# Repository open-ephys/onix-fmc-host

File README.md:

# ONIX FMC Host
This card provides a host interface for serialized headstages and miniscopes, as
well as general purpose analog and digital IO. It is a VITA-57.1
compliant module that uses high pin-count FMC connector. In combination with a
base FPGA board (e.g. [Numato Lab
Nereid](https://numato.com/product/nereid-kintex-7-pci-express-fpga-development-board),
it provides host PC communication for the following:

- Two deserailizers for any multifunction headstage conforming to the ONIX
  serialization protocol
- 12x 16-bit, +/-10V analog outputs or inputs. Direction selected via analog
  switch controllable over the FMC connector. Analog inputs are separated into
  2 simultaneously sampled 6-channel banks. 
- Analog output are always looped back using the analog inputs.
- 3x high speed LVDS input pairs
- 2x high speed LVDS outputs pairs
- 2x high speed, arbitrary logic-level, singled-ended Hi-Z or 50-ohm clock inputs
- 1x high speed single ended, 50-ohm clock output
- 4x MLVDS input or output trigger lines

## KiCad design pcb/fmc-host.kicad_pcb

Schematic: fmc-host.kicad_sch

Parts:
C1, C2, C5, C6, C26, C27, C34, C35, C36, C37, C70, C71, C72, C73, C79, C80, C81, C91, C92, C106, C118, C139, C140: 10uF; 1206; MPN GRM31CR71E106KA12L
C3, C4, C7, C8, C9, C10, C13, C14, C15, C16, C17, C18, C19, C22, C23, C30, C31, C32, C33, C41, C43, C44, C45, C46, C47, C48, C49, C52, C53, C54, C55, C56, C60, C61, C63, C65, C67, C68, C78, C83, C84, C85, C86, C87, C89, C90, C93, C99, C100, C104, C107, C110, C111, C112, C114, C132, C134, C135, C137, C138, C141, C142: 0.1uF; 0402; Voltage 25V; MPN GRM155R71E104KE14D
C11, C12, C20, C21, C24, C25, C50, C51, C57, C58, C82, C122, C123, C124: 10nF; 0402; MPN GCM155R71E103KA37D
C28, C29: 4.7nF; 0402; MPN CC0402KRX7R8BB472
C38, C39: 47nF; 0402; MPN GRM155R71E473KA88D
C40, C42, C64, C66, C74, C75, C76, C88: 1uF; 0805; MPN GCM21BR71E105KA56L
C59, C62, C69, C77, C95, C96, C101, C103, C105, C108, C109, C113, C116, C117, C119, C120, C121, C125, C126, C127: 10uF; 0805; MPN GRM21BR61E106KA73L
C94, C97, C98, C102, C130, C131: 47uF; 1210; MPN TMK325ABJ476MM-T
C115: 100pF; 0402; MPN CC0402JRNPO9BN101
C128, C129: 0.1uF, 500V; 1210; MPN C1210C104KCRACTU
C133, C136: 33uF; 1411-VISHAY-B; MPN TL8B0336M020C
D1, D2: SESD0402X1UN-0030-088; 0402P-DFN; MPN SESD0402X1UN-0030-088
D3, D4, D5: BAR66; SOT23; MPN BAR66E6327HTSA1
D6: KDZVTR4.3B; SOD123; MPN KDZVTR4.3B
F1, F2, F3: C014F-2; 1812; MPN MINISMDC014F-2
J1, J2, J3, J4, J5: 6-1634010-0; MMCX-THRU; MPN 262105
J6: FTSH-105-01-F-D-RA-K; MPN FTSH-105-01-F-D-RA-K
J7: 12226-8250-00FR; 12226-82X0-00XX; MPN 12226-8250-00FR
J8: FMC_SINGLE_WIDTH_MODULE; not fitted
J9: ASP-134488-01; FMC_HPC_MALE; MPN ASP-134488-01
J10: BM08B-SURS-TF; MPN BM08B-SURS-TF
L1, L2: 1008PS-472; 1008PS; MPN 1008PS-472KLC
L3, L4, L9, L10, L11, L12: BLM18KG601SN1D; 0603; MPN BLM18KG601SN1D
L5, L6: SRN6045TA-101M; SRN6045TA; MPN SRN6045TA-101M
L7, L8: MPZ2012S102AT000; 0805; MPN MPZ2012S102AT000
L13: 1277AS-H-6R8M=P2; 1210; MPN 1277AS-H-6R8M=P2
L14, L15, L16, L17, L18, L19: BLM15PX601SN1D; 0402; MPN BLM15PX601SN1D
Q1, Q2, Q3, Q4: SI1012R; SC75; MPN SI1012CR-T1-GE3
R1, R2, R38, R39: 3k; 0402; MPN ERJ-2RKF3001X
R3, R4, R9, R10, R57, R58: 2k; 0402; MPN ERJ-2RKF2001X
R5, R6, R7, R8, R11, R12: 150,0.25W; 0603; MPN CRGP0603F150R
R13, R14, R49, R50, R51, R52, R76, R83, R84: 165k; 0402; MPN ERJ-2RKF1653X
R15, R16, R35, R37, R59, R63, R64, R65, R67, R68, R78, R79, R82: 10k; 0402; MPN ERJ-2RKF1002X
R17, R18, R41, R42, R44, R45, R46, R47: 1k; 0402; MPN ERJ-2RKF1001X
R19, R21: 5.6k 1%; 0402; MPN ERJ-2RKF5601X
R20, R22: 21k 1%; 0402; MPN ERJ-2RKF2102X
R23, R24, R28, R29: 49.9; 0402; MPN RR0510R-49R9-D
R25, R26, R27: 100; 0402; MPN ERJ-2RKF1000X
R30, R31, R32, R33, R40, R43, R71, R73, R75: 4.7k; 0402; MPN ERJ-2RKF4701X
R34, R36: DNP; 0402; MPN DNP; not fitted
R48, R66: 0; 0402; MPN RC0402JR-070RL
R53, R54, R55, R56: 2.2k; RN2X8-1506; MPN EXB-2HV222JV
R60, R61: 3.48k; 0402; MPN ERJ-2RKF3481X
R62: 649k; 0402; MPN ERJ-2RKF6493X
R69: 2.2k; 0402; MPN ERJ-2RKF2201X
R70: 15k; 0402; MPN ERJ-2RKF1502X
R72, R74: 47k; 0402; MPN ERJ-2RKF4702X
R77: 178k; 0402; MPN ERJ-2RKF1783X
R80, R81: 73.2k; 0402; MPN ERJ-2RKF7322X
R289, R290: 4.7,1W; R_1206_3216Metric; MPN SG73P2BTTD4R7J
S1, S2: CHS-01TA; DIP01-SMD-GULL; MPN CHS-01TA; not fitted
S3: CHS-02TB; MPN CHS-02TB
TP1, TP2, TP4, TP5, TP6, TP7, TP11, TP12, TP13, TP14, TP15, TP16: TPB1,27; B1,27
TP3, TP8, TP9, TP10, TP17, TP18: TPB2,54; B2,54
U1: SN74LVC2G34DCKR; SC70; MPN SN74LVC2G34DCKR
U2: SN65LVDS9638DGN; MSOP-8-PAD-3X3; MPN SN65LVDS9638DGN
U3: FIN1032MTCX; TSSOP-16; MPN FIN1032MTCX
U4, U5: ADCMP600; SOT-23-5; MPN ADCMP600BRJZ-R2
U6, U7, U8: DG1412E; QFN16-4X4MM; MPN DG1412EEN-T1-GE4
U9, U10: DS90UB934-Q1; WQFN48-7X7-PAD; MPN DS90UB934TRGZRQ1
U11: DS91M040; WQFN32-5X5; MPN DS91M040TSQ/NOPB
U12: AD5766BCPZ-RL7; CP_40_7; MPN AD5766BCPZ-RL7
U13: MCP47FEB02A0-E/ST; TSSOP-8; MPN MCP47FEB02A0-E/ST
U14: LM4132AMF-2.5/NOPB; SOT-23-5; MPN LM4132AMF-2.5/NOPB
U15: AD7616BSTZ; ST_80_2; MPN AD7616BSTZ
U16: AD5142BRUZ10; TSSOP-16_4.4X5.0; MPN AD5142BRUZ10
U17: LTM4622A; BGA_5X5_625X625; MPN LTM4622AIY#PBF
U18, U25, U26: D3V3XA4B10LP; Diodes_UDFN-10_1.0x2.5mm_P0.5mm; MPN D3V3XA4B10LP-7
U19, U20: TPS7A49; PVSON-N8+4-3X3; MPN TPS7A4901DRBR
U21: TPS7A30; PVSON-N8+4-3X3; MPN TPS7A3001DRBT
U22: 24AA64-I/ST; TSSOP8; MPN 24AA64-I/ST
U23: LTM8049IY#PBF; LTM8049; MPN LTM8049IY#PBF
U24: TPS62061DSGT; WSON8-2X2; MPN TPS62061DSGT
U27: TLV9062IDSGR; WSON-8-1EP_2x2mm_P0.5mm_EP0.9x1.6mm; MPN TLV9062IDSGR
U28: SN74LVC2G14DBV; SOT-23-6; MPN SN74LVC2G14DBVR
X2: OE-LOGO_7X5; OE-LOGO-7X5

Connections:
+1V8: C86.2, C87.2, C91.2, C92.2, C106.2, L3.2, L4.2, L9.1, L10.1, L13.1, R19.1, R21.1, R34.1, R36.1, TP16.TP (TP_TP), U9.17 (VDD18), U10.17 (VDD18), U24.4 (FB)
+3V3: C10.2, C22.1, C23.1, C28.1, C29.1, C32.1, C33.1, C74.2, C78.2, C82.2, C89.2, C93.2, C96.2, C111.2, C113.2, C114.2, C117.2, C118.2, C136.A (+), C137.2, C138.2, C139.1, C140.1, C141.1, C142.1, J9.E39 (VADJ@1), J9.F40 (VADJ@2), J9.G39 (VADJ@1), J9.H40 (VADJ@2), J9.J39 (VIO_B_M2C@1), J9.K40 (VIO_B_M2C@2), L11.1, L12.1, R30.2, R31.2, R32.2, R33.2, R40.2, R43.2, R57.2, R58.2, R64.1, R65.1, R69.1, R78.2, R79.2, S1.2, S2.2, TP11.TP (TP_TP), U1.5 (VCC), U2.1 (VCC), U3.4 (EN), U3.16 (VCC), U4.5 (V+), U5.5 (V+), U9.4 (OSS_SEL), U9.5 (OEN), U10.4 (OSS_SEL), U10.5 (OEN), U11.11 (VDD), U11.12 (VDD), U11.29 (VDD), U11.30 (VDD), U12.4 (VLOGIC), U13.1 (VDD), U13.2 (REFA), U15.49 (VDRIVE), U16.1 (INDEP), U16.11 (VDD), U16.12 (VLOGIC), U23.A5 (VIN1), U23.A6 (VIN1), U23.A7 (VIN1), U23.B7 (RUN1), U23.K7 (RUN2), U23.L5 (VIN2), U23.L6 (VIN2), U23.L7 (VIN2), U24.5 (EN), U24.6 (MODE), U24.7 (AVIN), U24.8 (PVIN), U27.8 (V+), U28.5 (V_{CC})
+12V: C116.2, C133.A (+), C134.2, C135.2, J7.1, J7.26, J9.C35 (12P0V1), J9.C37 (12P0V2), R38.2, R39.2, TP12.TP (TP_TP), U17.A2 (VIN), U17.B3 (VIN), U17.D3 (VIN), U17.E2 (VIN)
/+5V_AN: C59.2, C62.2, C69.2, C77.2, C81.1, C83.2, C84.2, C85.2, C90.2, C107.2, C108.2, L14.1, TP1.TP (TP_TP), U12.28 (AVCC), U14.3 (EN), U14.4 (VIN), U15.6 (VCC), U15.15 (VCC), U15.30 (VCC), U15.71 (VCC)
/+13V_AN: C7.2, C8.2, C9.2, C104.2, C105.2, L15.1, TP2.TP (TP_TP), U6.11 (V+), U7.11 (V+), U8.11 (V+), U12.26 (AVDD)
/-13V_AN: C17.2, C18.2, C19.2, C99.2, C103.2, L16.1, TP4.TP (TP_TP), U6.2 (V-), U6.PAD (V-), U7.2 (V-), U7.PAD (V-), U8.2 (V-), U8.PAD (V-), U12.6 (AVSS), U12.PAD (AVSS)
/ADC_BUSY: J9.J12 (HA11_P), U15.67 (BUSY)
/ADC_CONVST: J9.K13 (HA10_P), U15.68 (CONVST)
/ADC_MISO_A: J9.K11 (HA06_N), U15.57 (DB12/SDOA)
/ADC_MISO_B: J9.J10 (HA07_N), U15.56 (DB11/SDOB)
/ADC_MOSI: J9.K10 (HA06_P), U15.55 (DB10/SDI)
/ADC_SCLK: J9.J13 (HA11_N), U15.62 (SCLK/~RD)
/ADDR0: J9.C27 (LA27_N), R78.1, S3.4
/ADDR1: J9.C26 (LA27_P), R79.1, S3.3
/AIN_AOUT0: J9.F11 (HA08_N), U8.15 (IN1)
/AIN_AOUT1: J9.D11 (LA05_P), U8.6 (IN4)
/AIN_AOUT2: J9.E12 (HA13_P), U8.7 (IN3)
/AIN_AOUT3: J9.H10 (LA04_P), U8.14 (IN2)
/AIN_AOUT4: J9.E18 (HA20_P), U7.15 (IN1)
/AIN_AOUT5: J9.J9 (HA07_P), U7.6 (IN4)
/AIN_AOUT6: J9.G10 (LA03_N), U7.7 (IN3)
/AIN_AOUT7: J9.F17 (HA15_N), U7.14 (IN2)
/AIN_AOUT8: J9.H20 (LA15_N), U6.7 (IN3)
/AIN_AOUT9: J9.J19 (HA18_N), U6.14 (IN2)
/AIN_AOUT10: J9.G19 (LA16_N), U6.6 (IN4)
/AIN_AOUT11: J9.H19 (LA15_P), U6.15 (IN1)
/AIO_0: J7.7, R53.C1, U8.16 (D1)
/AIO_1: J7.20, R53.C3, U8.5 (D4)
/AIO_2: J7.8, R53.C5, U8.8 (D3)
/AIO_3: J7.21, R53.C8, U8.13 (D2)
/AIO_4: J7.9, R54.C4, U7.16 (D1)
/AIO_5: J7.22, R54.C2, U7.5 (D4)
/AIO_6: J7.10, R56.C5, U7.8 (D3)
/AIO_7: J7.23, R56.C7, U7.13 (D2)
/AIO_8: J7.11, R55.C6, U6.8 (D3)
/AIO_9: J7.24, R55.C8, U6.13 (D2)
/AIO_10: J7.12, R55.C4, U6.5 (D4)
/AIO_11: J7.25, R55.C1, U6.16 (D1)
/AOUT0: U6.1 (S1), U12.32 (VOUT0)
/AOUT1: U6.4 (S4), U12.33 (VOUT1)
/AOUT2: U6.9 (S3), U12.34 (VOUT2)
/AOUT3: U6.12 (S2), U12.35 (VOUT3)
/AOUT4: U7.1 (S1), U12.36 (VOUT4)
/AOUT5: U7.4 (S4), U12.37 (VOUT5)
/AOUT6: U7.12 (S2), U12.38 (VOUT6)
/AOUT7: U7.9 (S3), U12.39 (VOUT7)
/AOUT8: U8.9 (S3), U12.12 (VOUT8)
/AOUT9: U8.12 (S2), U12.13 (VOUT9)
/AOUT10: U8.4 (S4), U12.14 (VOUT10)
/AOUT11: U8.1 (S1), U12.15 (VOUT11)
/CLKIN0: J9.D21 (LA17_N_CC), TP7.TP (TP_TP), U4.1 (OUT)
/CLKIN1: J9.E19 (HA20_N), TP6.TP (TP_TP), U5.1 (OUT)
/CLKIN_TERM0: J9.K19 (HA21_P), R17.1
/CLKIN_TERM1: J9.K17 (HA17_N_CC), R18.1
/CLKIN_VBIAS_SCL: J9.J21 (HA22_P), R58.1, U13.7 (SCL)
/CLKIN_VBIAS_SDA: J9.K20 (HA21_N), R57.1, U13.8 (SDA)
/CLKOUT: J9.D20 (LA17_P_CC), U1.1 (IN3), U1.3 (IN2)
/DAC_MISO: J9.K16 (HA17_P_CC), U12.9 (MISO)
/DAC_MOSI: J9.H14 (LA07_N), U12.5 (MOSI)
/DAC_SCLK: J9.J15 (HA14_P), U12.7 (SCLK)
/DES_A_D0: J9.F34 (HB16_P), U10.24 (ROUT0)
/DES_A_D1: J9.K35 (HB14_N), U10.23 (ROUT1)
/DES_A_D2: J9.J34 (HB15_N), U10.22 (ROUT2)
/DES_A_D3: J9.K34 (HB14_P), U10.21 (ROUT3)
/DES_A_D4: J9.E33 (HB19_P), U10.19 (ROUT4)
/DES_A_D5: J9.J33 (HB15_P), U10.18 (ROUT5)
/DES_A_D6: J9.F32 (HB12_N), U10.16 (ROUT6)
/DES_A_D7: J9.E31 (HB13_N), U10.15 (ROUT7)
/DES_A_D8: J9.K32 (HB10_N), U10.14 (ROUT8)
/DES_A_D9: J9.F31 (HB12_P), U10.13 (ROUT9)
/DES_A_D10: J9.J31 (HB11_N), U10.12 (ROUT10)
/DES_A_D11: J9.K31 (HB10_P), U10.11 (ROUT11)
/DES_A_GPIO0: J9.J37 (HB18_N), U10.28 (GPIO0)
/DES_A_GPIO1: J9.K37 (HB17_P_CC), U10.27 (GPIO1)
/DES_A_GPIO2: J9.J36 (HB18_P), U10.26 (GPIO2)
/DES_A_GPIO3: J9.E34 (HB19_N), R43.1, U10.25 (GPIO3/INTB)
/DES_A_HSYNC: J9.E30 (HB13_P), U10.10 (HSYNC)
/DES_A_LOCK: J9.E27 (HB09_P), R50.2, U10.48 (LOCK)
/DES_A_PASS: J9.J28 (HB07_N), R52.2, U10.47 (PASS)
/DES_A_PCLK: J9.K28 (HB06_P_CC), U10.8 (PCLK)
/DES_A_PDB: J9.F35 (HB16_N), U10.30 (PDB)
/DES_A_SCL: J9.F29 (HB08_N), R31.1, U10.2 (SCL)
/DES_A_SDA\: J9.E28 (HB09_N), R33.1, U10.1 (SDA)
/DES_A_VSYNC: J9.J30 (HB11_P), U10.9 (VSYNC)
/DES_B_D0: J9.H29 (LA24_N), U9.24 (ROUT0)
/DES_B_D1: J9.H28 (LA24_P), U9.23 (ROUT1)
/DES_B_D2: J9.G28 (LA25_N), U9.22 (ROUT2)
/DES_B_D3: J9.G27 (LA25_P), U9.21 (ROUT3)
/DES_B_D4: J9.D27 (LA26_N), U9.19 (ROUT4)
/DES_B_D5: J9.D26 (LA26_P), U9.18 (ROUT5)
/DES_B_D6: J9.H26 (LA21_N), U9.16 (ROUT6)
/DES_B_D7: J9.G25 (LA22_N), U9.15 (ROUT7)
/DES_B_D8: J9.H25 (LA21_P), U9.14 (ROUT8)
/DES_B_D9: J9.D24 (LA23_N), U9.13 (ROUT9)
/DES_B_D10: J9.G24 (LA22_P), U9.12 (ROUT10)
/DES_B_D11: J9.D23 (LA23_P), U9.11 (ROUT11)
/DES_B_GPIO0: J9.H32 (LA28_N), U9.28 (GPIO0)
/DES_B_GPIO1: J9.G31 (LA29_N), U9.27 (GPIO1)
/DES_B_GPIO2: J9.H31 (LA28_P), U9.26 (GPIO2)
/DES_B_GPIO3: J9.G30 (LA29_P), R40.1, U9.25 (GPIO3/INTB)
/DES_B_HSYNC\: J9.H23 (LA19_N), U9.10 (HSYNC)
/DES_B_LOCK: J9.J22 (HA22_N), R49.2, U9.48 (LOCK)
/DES_B_PASS: J9.K22 (HA23_P), R51.2, U9.47 (PASS)
/DES_B_PCLK: J9.C22 (LA18_P_CC), U9.8 (PCLK)
/DES_B_PDB: J9.G33 (LA31_P), U9.30 (PDB)
/DES_B_SCL: J9.G22 (LA20_N), R30.1, U9.2 (SCL)
/DES_B_SDA: J9.H22 (LA19_P), R32.1, U9.1 (SDA)
/DES_B_VSYNC: J9.K23 (HA23_N), U9.9 (VSYNC)
/DI_VBIAS0: R15.1, U13.3 (VOUT0)
/DI_VBIAS1: R16.1, U13.4 (VOUT1)
/DOUTP_F_A: C45.2, D2.C, J2.SIG (1), L2.2, R4.2
/DOUTP_F_B: C44.2, D1.C, J1.SIG (1), L1.2, R3.2
/FMC_PG: J9.D1 (PG_C2M), J9.F1 (PG_M2C)
/LINK_A_PWR_EN: J9.H37 (LA32_P), R68.1, U17.B2 (RUN2), U28.1 (1A)
/LINK_B_PWR_EN: J9.K38 (HB17_N_CC), R67.1, U17.D2 (RUN1), U28.3 (2A)
/LINK_PWR_ADJ_MISO: J9.F37 (HB20_P), R69.2, U16.15 (MISO)
/LINK_PWR_ADJ_MOSI: J9.E36 (HB21_P), U16.14 (MOSI)
/LINK_PWR_ADJ_SCLK: J9.H38 (LA32_N), U16.13 (SCLK)
/LVDS_DIN0: J9.J2 (CLK3_M2C_P), U3.3 (AOUT)
/LVDS_DIN0_N: J7.4, R25.1, U3.1 (A-), U18.1, U18.10 (NC)
/LVDS_DIN0_P: J7.17, R25.2, U3.2 (A+), U18.2, U18.9 (NC)
/LVDS_DIN1: J9.H5 (CLK0_M2C_N), U3.5 (BOUT)
/LVDS_DIN1_N: J7.16, R26.1, U3.7 (B-), U18.5, U18.6 (NC)
/LVDS_DIN1_P: J7.3, R26.2, U3.6 (B+), U18.4, U18.7 (NC)
/LVDS_DIN2: J9.H4 (CLK0_M2C_P), U3.11 (COUT)
/LVDS_DIN2_N: J7.2, R27.1, U3.9 (C-), U25.5
/LVDS_DIN2_P: J7.15, R27.2, U3.10 (C+), U25.4
/LVDS_DOUT0: J9.J3 (CLK3_M2C_N), U2.2 (AIN)
/LVDS_DOUT0_N: J7.19, U2.7 (AOUT-), U26.4, U26.7 (NC)
/LVDS_DOUT0_P: J7.6, U2.8 (AOUT+), U26.5, U26.6 (NC)
/LVDS_DOUT1: J9.K4 (CLK2_M2C_P), U2.3 (BIN)
/LVDS_DOUT1_N: J7.18, U2.5 (BOUT-), U26.1, U26.10 (NC)
/LVDS_DOUT1_P: J7.5, U2.6 (BOUT+), U26.2, U26.9 (NC)
/MLVDS_CLK_0_N: J6.10, U11.24 (B0)
/MLVDS_CLK_0_P: J6.09 (9), U11.23 (A0)
/MLVDS_CLK_1_N: J6.08 (8), U11.22 (B1)
/MLVDS_CLK_1_P: J6.07 (7), U11.21 (A1)
/MLVDS_CLK_2_N: J6.04 (4), U11.20 (B2)
/MLVDS_CLK_2_P: J6.03 (3), U11.19 (A2)
/MLVDS_CLK_3_N: J6.02 (2), U11.18 (B3)
/MLVDS_CLK_3_P: J6.01 (1), U11.17 (A3)
/MLVDS_DE_~RE0: J9.F7 (HA04_P), U11.25 (DE0), U11.26 (~RE0)
/MLVDS_DE_~RE1: J9.E7 (HA05_N), U11.27 (DE1), U11.28 (~RE1)
/MLVDS_DE_~RE2: J9.H7 (LA02_P), U11.13 (~RE2), U11.14 (DE2)
/MLVDS_DE_~RE3: J9.H8 (LA02_N), U11.15 (~RE3), U11.16 (DE3)
/MLVDS_DI0: J9.F5 (HA00_N_CC), U11.2 (DI0)
/MLVDS_DI1: J9.E2 (HA01_P_CC), U11.4 (DI1)
/MLVDS_DI2: J9.E3 (HA01_N_CC), U11.6 (DI2)
/MLVDS_DI3: J9.G3 (CLK1_M2C_N), U11.8 (DI3)
/MLVDS_EN: J9.F8 (HA04_N), U11.10 (MDE)
/MLVDS_RO0: J9.F4 (HA00_P_CC), U11.1 (RO0)
/MLVDS_RO1: J9.G6 (LA00_P_CC), U11.3 (RO1)
/MLVDS_RO2: J9.G7 (LA00_N_CC), U11.5 (RO2)
/MLVDS_RO3: J9.G2 (CLK1_M2C_P), U11.7 (RO3)
/PORT_A_BLUE: J9.G18 (LA16_P), R41.2
/PORT_A_GREEN: J9.J18 (HA18_P), R47.2
/PORT_A_RED: J9.H17 (LA11_N), R42.1
/PORT_B_BLUE: J9.H16 (LA11_P), R45.2
/PORT_B_GREEN: J9.G15 (LA12_P), R46.2
/PORT_B_RED: J9.G13 (LA08_N), R44.2
/SCL: J9.C30 (SCL), U22.6 (SCL)
/SDA: J9.C31 (SDA), U22.5 (SDA)
/TDI-TDO: J9.D30 (TDI), J9.D31 (TDO)
/VAUX: C132.2, J9.D32 (3P3VAUX), U22.8 (VCC)
/VDD_FPDX_A: C2.2, C4.2, C12.2, C21.2, C25.2, L4.1, U10.31 (VDD18_FPD1), U10.40 (VDD18_FPD0)
/VDD_FPDX_B: C1.2, C3.2, C11.2, C20.2, C24.2, L3.1, U9.31 (VDD18_FPD1), U9.40 (VDD18_FPD0)
/VDD_PX_A: C49.2, C51.2, C54.2, C58.2, C65.2, C72.2, L10.2, U10.36 (VDD18_P1), U10.45 (VDD18_P0)
/VDD_PX_B: C48.2, C50.2, C53.2, C57.2, C63.2, C70.2, L9.2, U9.36 (VDD18_P1), U9.45 (VDD18_P0)
/VLINK_A: C27.2, C31.1, C94.2, C97.2, L8.1, Q3.3 (D), TP13.TP (TP_TP), U17.A1 (VOUT2), U17.B1 (VOUT2)
/VLINK_B: C26.2, C30.1, C98.2, C102.2, L7.1, Q4.3 (D), TP14.TP (TP_TP), U17.D1 (VOUT1), U17.E1 (VOUT1)
/VREF: C88.2, R59.2, U12.22 (VREF), U14.5 (VOUT)
/V_PROTECT: C52.2, D3.2 (C), D4.2 (C), D5.2 (C), D6.C, R38.1, R39.1, TP5.TP (TP_TP)
/~ADC_CS: J9.H13 (LA07_P), U15.63 (~CS)
/~ADC_RESET: J9.F10 (HA08_P), R66.2
/~DAC_CS: J9.J16 (HA14_N), U12.8 (~CS)
/~DAC_RESET: J9.F14 (HA12_N), U12.3 (~RESET)
/~LINK_PWR_ADJ_CS: J9.F38 (HB20_N), U16.16 (~CS)
/~LINK_PWR_ADJ_RESET: J9.E37 (HB21_N), U16.2 (~RESET)
AGND: C7.1, C8.1, C9.1, C17.1, C18.1, C19.1, C59.1, C62.1, C69.1, C77.1, C81.2, C83.1, C84.1, C85.1, C88.1, C90.1, C95.1, C99.1, C100.1, C101.1, C103.1, C104.1, C105.1, C107.1, C108.1, J7.13, J7.14, R48.1, R53.C2, R53.C4, R53.C6, R53.C7, R54.C1, R54.C3, R54.C5, R54.C6, R54.C7, R54.C8, R55.C2, R55.C3, R55.C5, R55.C7, R56.C1, R56.C2, R56.C3, R56.C4, R56.C6, R56.C8, TP3.TP (TP_TP), U6.3 (GND), U7.3 (GND), U8.3 (GND), U12.10 (AGND), U12.20 (NIC), U12.23 (N0), U12.24 (N1), U12.25 (NIC), U12.29 (AGND), U12.31 (NIC), U14.2 (GND), U15.5 (AGND), U15.16 (AGND), U15.29 (AGND), U15.32 (REFGND), U15.34 (REFINOUTGND), U15.69 (REGGND), U15.72 (AGND)
GND: C1.1, C2.1, C3.1, C4.1, C5.1, C6.1, C10.1, C11.1, C12.1, C13.2, C14.2, C15.2, C16.2, C20.1, C21.1, C22.2, C23.2, C24.1, C25.1, C26.1, C27.1, C28.2, C29.2, C30.2, C31.2, C32.2, C33.2, C34.1, C35.1, C36.1, C37.1, C40.1, C41.1, C42.1, C43.1, C46.1, C47.1, C48.1, C49.1, C50.1, C51.1, C52.1, C53.1, C54.1, C55.1, C56.1, C57.1, C58.1, C60.1, C61.1, C63.1, C64.1, C65.1, C66.1, C67.1, C68.1, C70.1, C71.1, C72.1, C73.1, C74.1, C75.1, C76.1, C78.1, C79.1, C80.1, C82.1, C86.1, C87.1, C89.1, C91.1, C92.1, C93.1, C94.1, C96.1, C97.1, C98.1, C102.1, C106.1, C109.1, C110.1, C111.1, C112.1, C113.1, C114.1, C115.2, C116.1, C117.1, C118.1, C119.1, C120.1, C121.1, C122.2, C123.2, C124.2, C125.1, C126.1, C127.1, C128.1, C129.1, C130.1, C131.2, C132.1, C133.C (-), C134.1, C135.1, C136.C (-), C137.1, C138.1, C139.2, C140.2, C141.2, C142.2, D1.A, D2.A, D3.1 (A), D4.1 (A), D5.1 (A), D6.A, J1.GND@1 (2), J1.GND@2 (2), J1.GND@3 (2), J1.GND@4 (2), J2.GND@1 (2), J2.GND@2 (2), J2.GND@3 (2), J2.GND@4 (2), J3.GND@1 (2), J3.GND@2 (2), J3.GND@3 (2), J3.GND@4 (2), J4.GND@1 (2), J4.GND@2 (2), J4.GND@3 (2), J4.GND@4 (2), J5.GND@1 (2), J5.GND@2 (2), J5.GND@3 (2), J5.GND@4 (2), J6.05 (5), J6.06 (6), J7.PAD1, J7.PAD2, J9.A1 (GND@1), J9.A4 (GND@2), J9.A5 (GND@3), J9.A8 (GND@4), J9.A9 (GND@5), J9.A12 (GND@6), J9.A13 (GND@7), J9.A16 (GND@8), J9.A17 (GND@9), J9.A20 (GND@10), J9.A21 (GND@11), J9.A24 (GND@12), J9.A25 (GND@13), J9.A28 (GND@14), J9.A29 (GND@15), J9.A32 (GND@16), J9.A33 (GND@17), J9.A36 (GND@18), J9.A37 (GND@19), J9.A40 (GND@20), J9.B2 (GND@21), J9.B3 (GND@22), J9.B6 (GND@23), J9.B7 (GND@24), J9.B10 (GND@25), J9.B11 (GND@26), J9.B14 (GND@27), J9.B15 (GND@28), J9.B18 (GND@29), J9.B19 (GND@30), J9.B22 (GND@31), J9.B23 (GND@32), J9.B26 (GND@33), J9.B27 (GND@34), J9.B30 (GND@35), J9.B31 (GND@36), J9.B34 (GND@37), J9.B35 (GND@38), J9.B38 (GND@39), J9.B39 (GND@40), J9.C1 (GND@1), J9.C4 (GND@2), J9.C5 (GND@3), J9.C8 (GND@4), J9.C9 (GND@5), J9.C12 (GND@6), J9.C13 (GND@7), J9.C16 (GND@8), J9.C17 (GND@9), J9.C20 (GND@10), J9.C21 (GND@11), J9.C24 (GND@12), J9.C25 (GND@13), J9.C28 (GND@14), J9.C29 (GND@15), J9.C32 (GND@16), J9.C33 (GND@17), J9.C34 (GA0), J9.C36 (GND@18), J9.C38 (GND@19), J9.C40 (GND@20), J9.D2 (GND@21), J9.D3 (GND@22), J9.D6 (GND@23), J9.D7 (GND@24), J9.D10 (GND@25), J9.D13 (GND@26), J9.D16 (GND@27), J9.D19 (GND@28), J9.D22 (GND@29), J9.D25 (GND@30), J9.D28 (GND@31), J9.D35 (GA1), J9.D37 (GND@32), J9.D39 (GND@33), J9.E1 (GND@1), J9.E4 (GND@2), J9.E5 (GND@3), J9.E8 (GND@4), J9.E11 (GND@5), J9.E14 (GND@6), J9.E17 (GND@7), J9.E20 (GND@8), J9.E23 (GND@9), J9.E26 (GND@10), J9.E29 (GND@11), J9.E32 (GND@12), J9.E35 (GND@13), J9.E38 (GND@14), J9.E40 (GND@15), J9.F2 (GND@16), J9.F3 (GND@17), J9.F6 (GND@18), J9.F9 (GND@19), J9.F12 (GND@20), J9.F15 (GND@21), J9.F18 (GND@22), J9.F21 (GND@23), J9.F24 (GND@24), J9.F27 (GND@25), J9.F30 (GND@26), J9.F33 (GND@27), J9.F36 (GND@28), J9.F39 (GND@29), J9.G1 (GND@1), J9.G4 (GND@2), J9.G5 (GND@3), J9.G8 (GND@4), J9.G11 (GND@5), J9.G14 (GND@6), J9.G17 (GND@7), J9.G20 (GND@8), J9.G23 (GND@9), J9.G26 (GND@10), J9.G29 (GND@11), J9.G32 (GND@12), J9.G35 (GND@13), J9.G38 (GND@14), J9.G40 (GND@15), J9.H2 (PRSNT_M2C_L), J9.H3 (GND@16), J9.H6 (GND@17), J9.H9 (GND@18), J9.H12 (GND@19), J9.H15 (GND@20), J9.H18 (GND@21), J9.H21 (GND@22), J9.H24 (GND@23), J9.H27 (GND@24), J9.H30 (GND@25), J9.H33 (GND@26), J9.H36 (GND@27), J9.H39 (GND@28), J9.J1 (GND@1), J9.J4 (GND@2), J9.J5 (GND@3), J9.J8 (GND@4), J9.J11 (GND@5), J9.J14 (GND@6), J9.J17 (GND@7), J9.J20 (GND@8), J9.J23 (GND@9), J9.J26 (GND@10), J9.J29 (GND@11), J9.J32 (GND@12), J9.J35 (GND@13), J9.J38 (GND@14), J9.J40 (GND@15), J9.K2 (GND@16), J9.K3 (GND@17), J9.K6 (GND@18), J9.K9 (GND@19), J9.K12 (GND@20), J9.K15 (GND@21), J9.K18 (GND@22), J9.K21 (GND@23), J9.K24 (GND@24), J9.K27 (GND@25), J9.K30 (GND@26), J9.K33 (GND@27), J9.K36 (GND@28), J9.K39 (GND@29), J10.2, J10.6, Q1.2 (S), Q2.2 (S), R1.1, R2.1, R13.1, R14.1, R20.2, R22.2, R28.2, R29.2, R35.2, R37.2, R48.2, R49.1, R50.1, R51.1, R52.1, R62.2, R63.1, R67.2, R68.2, R71.1, R73.1, R75.1, R80.2, R81.2, R82.1, R83.1, R84.1, R289.2, R290.2, S3.1, S3.2, TP8.TP (TP_TP), TP9.TP (TP_TP), TP10.TP (TP_TP), TP17.TP (TP_TP), TP18.TP (TP_TP), U1.2 (GND), U2.4 (GND), U2.PAD (GND), U3.8 (GND), U3.12 (~EN), U4.2 (V-), U5.2 (V-), U9.43 (RES1), U9.44 (RES2), U9.46 (SEL), U9.PAD (GND), U10.43 (RES1), U10.44 (RES2), U10.46 (SEL), U10.PAD (GND), U11.31 (GND), U11.PAD (GND), U12.2 (DGND), U13.5 (AVSS), U13.6 (LAT/HVC), U15.37 (SEQEN), U15.38 (HW_RNGSEL1), U15.39 (HW_RNGSEL0), U15.41 (DB0), U15.42 (DB1), U15.43 (DB2), U15.44 (DB3), U15.46 (DB5/CRCEN), U15.47 (DB6), U15.48 (DB7), U15.50 (DGND), U15.51 (REGGNDD), U15.53 (DB8), U15.54 (DB9), U15.58 (DB13/OS0), U15.59 (DB14/OS1), U15.60 (DB15/OS2), U15.61 (WR~/BURST), U15.64 (CHSEL0), U15.65 (CHSEL1), U15.66 (CHSEL2), U16.3 (GND), U16.5 (W1), U16.7 (VSS), U16.9 (W2), U17.B5 (GND), U17.C1 (GND), U17.C2 (GND), U17.C5 (SYNC/MODE), U17.D5 (GND), U18.3 (VSS), U18.8 (VSS), U19.3 (NC), U19.4 (GND), U19.PAD1 (PAD), U19.PAD2 (PAD), U19.PAD3 (PAD), U19.PAD4 (PAD), U19.PAD5 (PAD), U20.3 (NC), U20.4 (GND), U20.PAD1 (PAD), U20.PAD2 (PAD), U20.PAD3 (PAD), U20.PAD4 (PAD), U20.PAD5 (PAD), U21.3 (NC), U21.4 (GND), U21.PAD1 (PAD), U21.PAD2 (PAD), U21.PAD3 (PAD), U21.PAD4 (PAD), U21.PAD5 (PAD), U22.1 (A0), U22.2 (A1), U22.3 (A2), U22.4 (GND), U22.7 (WP), U23.A3 (GND), U23.A4 (GND), U23.B3 (GND), U23.B4 (GND), U23.B5 (GND), U23.B6 (GND), U23.C2 (VOUT1N), U23.C3 (GND), U23.C4 (GND), U23.C5 (GND), U23.C6 (GND), U23.D1 (VOUT1N), U23.D2 (VOUT1N), U23.D3 (GND), U23.D4 (GND), U23.D5 (GND), U23.D7 (SYNC1), U23.E1 (VOUT1N), U23.E2 (VOUT1N), U23.E3 (GND), U23.E4 (GND), U23.E5 (GND), U23.F1 (GND), U23.F2 (GND), U23.F5 (GND), U23.F6 (GND), U23.F7 (GND), U23.G3 (GND), U23.G4 (GND), U23.G5 (GND), U23.H3 (GND), U23.H4 (GND), U23.H5 (GND), U23.J3 (GND), U23.J4 (GND), U23.J5 (GND), U23.J6 (GND), U23.K1 (VOUT2P), U23.K2 (VOUT2P), U23.K3 (GND), U23.K4 (GND), U23.K5 (GND), U23.K6 (GND), U23.L1 (VOUT2P), U23.L2 (VOUT2P), U23.L3 (GND), U23.L4 (GND), U24.1 (PGND), U24.3 (AGND), U24.PAD (AGND), U25.3 (VSS), U25.8 (VSS), U26.3 (VSS), U26.8 (VSS), U27.4 (V-), U27.9 (PAD), U28.2 (GND)
unnamed: C5.2, C15.1, L5.1, L7.2, R9.1
unnamed: C6.2, C16.1, L6.1, L8.2, R10.1
unnamed: C38.2, R28.1
unnamed: C39.2, R29.1
unnamed: C55.2, C60.2, C64.2, C71.2, L11.2, U9.7 (VDDIO), U9.29 (VDDIO)
unnamed: C56.2, C61.2, C66.2, C73.2, L12.2, U10.7 (VDDIO), U10.29 (VDDIO)
unnamed: C130.2, L17.2, L18.2, R76.1, U23.A1 (VOUT1P), U23.A2 (VOUT1P), U23.B1 (VOUT1P), U23.B2 (VOUT1P)
unnamed: C131.1, L19.2, R77.1, U23.G1 (VOUT2N), U23.G2 (VOUT2N), U23.H1 (VOUT2N), U23.H2 (VOUT2N), U23.J2 (VOUT2N)
unnamed: D3.3 (COMM), F3.2, U1.4 (OUT2), U1.6 (OUT1)
unnamed: D4.3 (COMM), F1.2, R1.2, R5.2, R7.2, R11.2, R23.1
unnamed: D5.3 (COMM), F2.2, R2.2, R6.2, R8.2, R12.2, R24.1
unnamed: F1.1, J3.SIG (1)
unnamed: F2.1, J4.SIG (1)
unnamed: F3.1, J5.SIG (1)
unnamed: C128.2, J9.CHASSIS_A (STANDOFF_A)
unnamed: C129.2, J9.CHASSIS_B (STANDOFF_B)
unnamed: J10.1, R44.1
unnamed: J10.3, R46.1
unnamed: J10.4, R45.1
unnamed: J10.5, R42.2
unnamed: J10.7, R47.1
unnamed: J10.8, R41.1
unnamed: L1.1, L5.2, R3.1, R9.2
unnamed: L2.1, L6.2, R4.1, R10.2
unnamed: Q1.3 (D), R5.1, R7.1, R11.1
unnamed: Q1.1 (G), R13.2, R17.2
unnamed: Q2.3 (D), R6.1, R8.1, R12.1
unnamed: Q2.1 (G), R14.2, R18.2
unnamed: Q3.1 (G), R83.2, U27.1
unnamed: Q3.2 (S), R289.1, U27.2 (-)
unnamed: Q4.1 (G), R84.2, U27.7
unnamed: Q4.2 (S), R290.1, U27.6 (-)
unnamed: R23.2, U4.3 (+IN)
unnamed: C13.1, R15.2, U4.4 (-IN)
unnamed: R24.2, U5.3 (+IN)
unnamed: C14.1, R16.2, U5.4 (-IN)
unnamed: S1.1, U9.6 (BISTEN)
unnamed: R34.2, R35.1, U9.35 (IDX)
unnamed: R19.2, R20.1, U9.37 (MODE)
unnamed: C44.1, U9.41 (RIN0+)
unnamed: C38.1, U9.42 (RIN0-)
unnamed: C34.2, C40.2, C46.2, U9.3 (VDD11_D)
unnamed: C35.2, C41.2, U9.20 (VDD11_DVP)
unnamed: C67.2, C75.2, C79.2, U9.34 (VDD11_FPD)
unnamed: S2.1, U10.6 (BISTEN)
unnamed: R36.2, R37.1, U10.35 (IDX)
unnamed: R21.2, R22.1, U10.37 (MODE)
unnamed: C45.1, U10.41 (RIN0+)
unnamed: C39.1, U10.42 (RIN0-)
unnamed: C36.2, C42.2, C47.2, U10.3 (VDD11_D)
unnamed: C37.2, C43.2, U10.20 (VDD11_DVP)
unnamed: C68.2, C76.2, C80.2, U10.34 (VDD11_FPD)
unnamed: TP15.TP (TP_TP), U12.27 (MUX_OUT)
unnamed: R65.2, U15.45 (DB4/~SER1WR)
unnamed: C95.2, U15.31 (REFCAP)
unnamed: C100.2, R59.1, U15.33 (REFINOUT)
unnamed: R63.2, U15.35 (REFSEL)
unnamed: C101.2, U15.70 (REGCAP)
unnamed: C109.2, U15.52 (REGCAPD)
unnamed: R64.2, U15.40 (SER/~PAR)
unnamed: R53.1, U15.28 (V0A)
unnamed: R53.2, U15.27 (V0AGND)
unnamed: R55.8, U15.73 (V0B)
unnamed: R55.7, U15.74 (V0BGND)
unnamed: R53.3, U15.26 (V1A)
unnamed: R53.4, U15.25 (V1AGND)
unnamed: R55.6, U15.75 (V1B)
unnamed: R55.5, U15.76 (V1BGND)
unnamed: R53.5, U15.24 (V2A)
unnamed: R53.6, U15.23 (V2AGND)
unnamed: R55.4, U15.77 (V2B)
unnamed: R55.3, U15.78 (V2BGND)
unnamed: R53.8, U15.22 (V3A)
unnamed: R53.7, U15.21 (V3AGND)
unnamed: R55.1, U15.79 (V3B)
unnamed: R55.2, U15.80 (V3BGND)
unnamed: R54.2, U15.19 (V4A)
unnamed: R54.1, U15.20 (V4AGND)
unnamed: R56.7, U15.2 (V4B)
unnamed: R56.8, U15.1 (V4BGND)
unnamed: R54.4, U15.17 (V5A)
unnamed: R54.3, U15.18 (V5AGND)
unnamed: R56.5, U15.4 (V5B)
unnamed: R56.6, U15.3 (V5BGND)
unnamed: R54.5, U15.14 (V6A)
unnamed: R54.6, U15.13 (V6AGND)
unnamed: R56.4, U15.7 (V6B)
unnamed: R56.3, U15.8 (V6BGND)
unnamed: R54.7, U15.12 (V7A)
unnamed: R54.8, U15.11 (V7AGND)
unnamed: R56.2, U15.9 (V7B)
unnamed: R56.1, U15.10 (V7BGND)
unnamed: C115.1, R66.1, R82.2, U15.36 (~RESET)
unnamed: R60.2, U16.4 (A1)
unnamed: R61.2, U16.8 (A2)
unnamed: R60.1, U17.E4 (FB1)
unnamed: R61.1, U17.A4 (FB2)
unnamed: R62.1, U17.C4 (FREQ)
unnamed: C112.2, U17.E3 (TRACK/SS1)
unnamed: C110.2, U17.A3 (TRACK/SS2)
unnamed: C125.2, L17.1, U19.5 (EN), U19.8 (IN)
unnamed: R70.1, R71.2, U19.2 (FB)
unnamed: C122.1, U19.6 (NR/SS)
unnamed: C119.2, L14.2, R70.2, U19.1 (OUT)
unnamed: C126.2, L18.1, U20.5 (EN), U20.8 (IN)
unnamed: R72.1, R73.2, U20.2 (FB)
unnamed: C123.1, U20.6 (NR/SS)
unnamed: C120.2, L15.2, R72.2, U20.1 (OUT)
unnamed: C127.2, L19.1, U21.5 (EN), U21.8 (IN)
unnamed: R74.1, R75.2, U21.2 (FB)
unnamed: C124.1, U21.6 (NR/SS)
unnamed: C121.2, L16.2, R74.2, U21.1 (OUT)
unnamed: U23.E6 (CLKOUT1), U23.H7 (SYNC2)
unnamed: R76.2, U23.C1 (FBX1)
unnamed: R77.2, U23.J1 (FBX2)
unnamed: R80.1, U23.E7 (RT1)
unnamed: R81.1, U23.G7 (RT2)
unnamed: L13.2, U24.2 (SW)
unnamed: U27.3 (+), U28.6 (1Y)
unnamed: U27.5 (+), U28.4 (2Y)

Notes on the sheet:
DNP
LINK POWER
LINK A
NB: Default VBIAS = 1.65V
L2 is the smallest package size I could find that barely meets current saturation requriements. An 8x8mm device that is probably safer is the Bourns SRN8040TA series.
FMC IO
NB: VLINK adjust. - Max step down ratio: 1 - (45e-9 *1.48e6) = 0.933 - So max voltage = 11.19 - Linear mode selected - R_AW = 0 : VLINK = 11.0V - R_AW = 5k : VLINK = 5.0V - General: VLINK = 36.24k/(3.48k + R_AW) + 0.6
TP2
NB: GA0 and GA1 define the LSBs of the EEPROM I2C address. We use 0x1010000
FMC MEZZANINE
ANALOG IO
NB: Pulled up to 3.3V on carrier
TP1
CLK IN 1
SYNC. TRIG.
CLK OUT
SYNC
TP5
NB: Freq = 1.48 MHz
Quad 2
PIN ADC DAC -------------------------- AIO_11 3B 0 AIO_10 2B 1 AIO_9 0B 3 AIO_8 1B 2 AIO_7 4B 6 AIO_6 5B 7 AIO_5 4A 5 AIO_4 5A 4 AIO_3 3A 9 AIO_2 2A 8 AIO_1 1A 10 AIO_0 0A 11
NB: TO MRCC Pin
Quad 1
PIN COUNTS - Total IO pins: 114 - LVDS pairs: 5 (TPs) - SE pins: 104 (Others) - LVDS CC pairs: 1 (TP0) - SE CC pins: 9 (PCLKs, DIs, DOs, MVLDSs)
NB: PCLK goes to dedicated MRCC pin
NB: DI0 and DO0 go to CC pins
TP3
Quad 3
NB: P,N order matches SDR datasheet spec.
PANEL RGB
NB: Standoff connectors on front bezel and on FMC connector should be isolated from GND and tied to chassis ground to form a star connection.
CLK IN 0
HPC FMC
CLOCK IO
NB: 3.48k = 11V output.
NB: Worst case 100 mA draw from both ADC and DAC. With 10V stepdown, this is 1W dissipation.
NB: VADJ must be set to 1.8V on host board~{}
NB: R-arrays provide input protection. Limit current thru internal clamp diodes to 10 mA at 20V.
NB: DC signals so no worries about DGND
NB: Input protection voltage ~4.6V

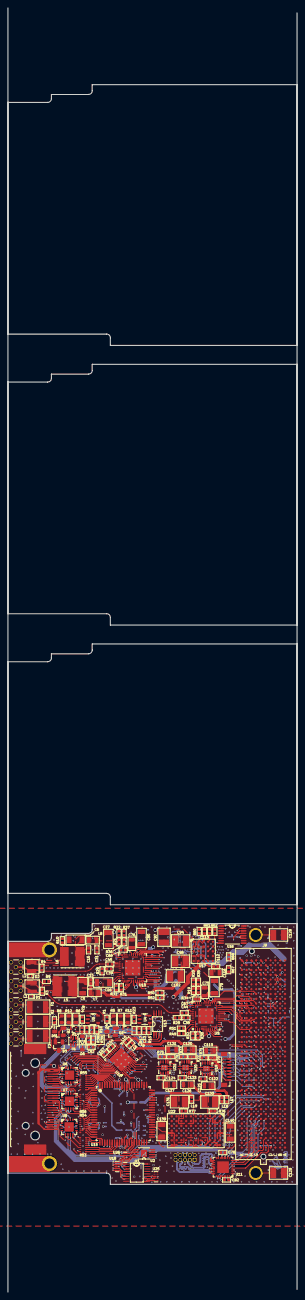
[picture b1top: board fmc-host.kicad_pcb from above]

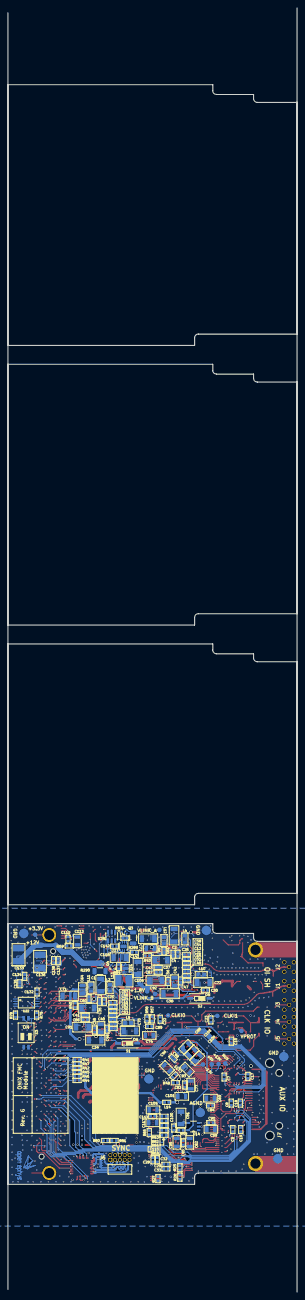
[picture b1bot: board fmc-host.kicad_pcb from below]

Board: 6 copper layers, 76.5 x 339.8 mm, 320 parts (163 on the bottom side), 300 nets.

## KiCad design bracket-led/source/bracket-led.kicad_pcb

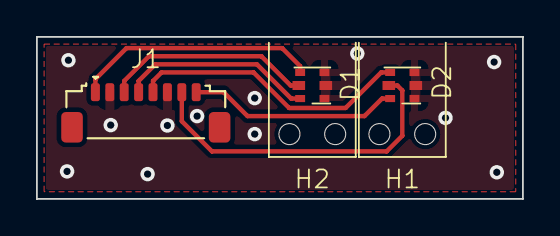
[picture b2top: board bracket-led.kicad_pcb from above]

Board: 2 copper layers, 27.0 x 9.0 mm, 5 parts (0 on the bottom side), 7 nets.

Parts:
D1, D2: LED_RGB; EVERLIGHT_6-SMD-1.6x1.6
H1, H2: SLP3-150-100-R; BIVAR_SLP3-150-100-R
J1: SM08B-SURS-TF(LF)(SN); JST_SM08B-SURS-TF(LF)(SN)

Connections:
B_{A}: D2.1 (BA), J1.8
B_{B}: D1.1 (BA), J1.4
GND: D1.2 (BK), D1.4 (RK), D1.6 (GK), D2.2 (BK), D2.4 (RK), D2.6 (GK), J1.2, J1.6
G_{A}: D2.5 (GA), J1.5
G_{B}: D1.5 (GA), J1.1
R_{A}: D2.3 (RA), J1.7
R_{B}: D1.3 (RA), J1.3

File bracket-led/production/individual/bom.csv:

Designator,Footprint,Quantity,Value,LCSC Part #
"D1, D2",EVERLIGHT_6-SMD-1.6x1.6,2,LED_RGB,C131204
"H1, H2",BIVAR_SLP3-150-100-R,2,SLP3-150-100-R,
J1,JST_SM08B-SURS-TF(LF)(SN),1,SM08B-SURS-TF(LF)(SN),C595161

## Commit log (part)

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2019-01-20 FMC host module
    - This will deprecate pcie-host
    - Should conform, largely, to VITA-57 standardFeatures
    - 1 deserializer
    - 2 arbitrary logic-level rugged GPIs
    - 1 arbitrary logic-level rugged GPO
    - 8 16-bit analog outputs
2019-01-20 Updates to fmc-host board
    - Added header for debug (need to connect still)
    - All test points to bottom
    - Silk screen improvements
2019-01-21 Completed fmc-host board
    - Added debug port that can be plugged into logic analyzer
    - Added pdf of schematic
    - Small silkscreen and routing changes
2019-01-23 fmc-host board v1.0
    - Ready for fabrication
    - BOM simplification
    - Part renumber
    - Silkscreen update
2019-01-25 Update READMEs to capture current state of project
    - fmc-host board
    - analog-io-board
    - pcie-host board removed from top level README
    - License files added where needed
2019-03-04 fmc-host updates after assembly
    - Mostly small layout changes to fix incorrect land patterns, shorts,
    etc.
    - Now we are using external reference for ADC and DAC instead of using
    ADC's
2019-03-05 Final updates to fmc-host rev 1.1
    - Changes reflect issues found during assembly
2019-03-05 Changed microstrip on fmc-host to match JLCPCB impednace specs
    - Using JLC7628
    - 50 Ohm trace is 0.3 mm thick (outer layer and first ground plane)
2019-05-07 Initial commit of 3d printed case for pcie fmc host Designed to slot into the FMC card and then screw into the numato board Many features and dimensions are still missing
2019-05-08 Tweaked pcie system case for initial test print
2019-05-23 Updated fmc pcie case - Fixed screw hole sizes (hopefully) - Less 90s design - Changed to 12mm FMC stack height
2019-07-28 Initial schematic for fmc-host rev. 1.1
    - High pincount FMC
    - Lots of feature additions and deprecations after learning from rev.
    1.0
    - 2x deserializers instead of 1
    - Remove 20 Ohm series impedance matching resistors from deserializer
    parallel connection because they are not needed
2019-07-30 Initial component placement for fmc-host rev. 1.1
    - 6 layer board with 2 high speed layers
    - Initial routing
    - Added a TODO file to the enclosure folder
2019-08-02 fmc-host rev 1.1 routing progress
    - Labelled all FMC pin connections by IO type and clock capability
    - Almost completely routed analog section (ADC, DAC, and muxing)
    - Starting to bring back digital IO to dummy vias on FMC for arrangement
2019-08-09 Initial FMC pinout largely decided
    - XDC file contains the pinout
    - Need to test sythesis before fully committing and finishing board
    routing
2019-08-12 fmc-host rev. 1.1
    - Completed revision 1.1 of the FMC host module
    - Needs final synthesis testing before fab
2019-08-15 Small fixes to silk layer on fmc-host rev 1.1
    - Should be ready for fabrication
    - Added some gerber art to gerber folder
2019-08-26 Replace SMD MMCX with thru hole on fmc-host
    - Less likely to rip off
    - Also, got rid of redundant ground vias around these connectors
2019-09-23 FMC host board rev. 1.3
    - Some minor changes after building revision 1.2 and implementing FPGA
    design
    - DES_A_PCLK moved to positive pin
    - Swapped DES_B_D[1] and DES_B_D[2]
    - Minor fixes to packages
    - BOM simplification
2019-09-29 Added CNCd PCIe bracket for FMC host
2019-09-30 Added text to pcie bracket
2019-09-30 Added STL of fmc-host PCIe bracket
2019-11-17 Updates to fmc-host board when testing revision 1.3
    - This is starting revision 1.4
    - Replaced SPDT analog switches for analog IO with SPST swiches inline
    with the analog outpus. Inputs are always connected. This allows
    loopback of analog output instead of wasting the analog input
    capabilites when a line is selected to be an output
2019-12-07 headstage-neuropix rev 1.2
    - Dual neuropixels probe support
    - 2X HTC Vive receivers
    - Many changes made for reliability of manufacturing
2020-01-06 fmc-host board rev. 1.4
    - Several small but significant changes to rev. 1.3
    - DES LOCK and PASS lines have pull down resistors now to deal with the
    fact that they are tri-stated when the DES is in PDN mode
    - PDN pin directly driven by FPGA instead of unnecessary FET
2020-02-07 fmc-host rev. 1.3
    - This revision of the fmc-host board addresses several issues
    encountered during testing of revision 1.2
    - The deserializers have been upgrated to DS90UB934-Q1s. This increases
    the forward channel bandwidth to 14 x 100 MHz and reduces back channel
    latency.
    - The SPDT analog switches on rev. 1.2 have been replaced with SDST
2020-02-07 Minor BOM simplifications to fmc-host rev. 1.3
2020-02-07 Updated PCIe mounting bracket
    - Increased FMC standoff form 10 to 12mm
    - Added holes for LEDs
    - Fixed markings
2020-02-09 Address Filipe's suggestions prior to fabrication
    - Use grid of cream bloks under QFN center pads instead of one large
    one. Place vias between these blocks where possible
    - Improve silk layer readability
    - Move copper away from dimension in several areas
    - Add SMD mount files
2020-02-09 Remove erroneos LED values from silk layer of fmc-host
2020-02-09 Move silk out from under components where possible in fmc-host
    - Bad practice, esp for passives, due to increase tombstoning risk
2020-02-12 Fixed LED cutouts for FMC and added little divider
2020-04-02 Added RGB LEDs and driver to breakout-board
    - The old circuit, with single green LEDs driven by the TCA9555 is still
    there and functional if this circuit is not populated
    - If it is, the LED outputs on the TCA should be set to hiZ
2020-06-08 Minor updates to fmc-host
    - Fix analog IO select mapping
    - Added html bom
2020-07-13 Added frozen fmc-host revision 1.4
    - This is the revision that was produced by OEPS for distribution with
    the beta test
2020-07-13 Started fmc-host revision 1.5
    - Added missing 2.2k pullup resistor to the MISO lines of the dual
    potentiometer, which is an open drain pin
2020-07-13 Got rid of accidentally added temporary files
2020-07-14 Moved the pullup resistor on fmc-host's pot's SDO line away from hole
    - It was too close to the FMC mounting hole and would have been smashed
    by the standoff
2020-08-28 Move entire repository to CC BY-NC-SA 4.0
2020-10-19 Added frozen fmc-host revision 1.3
    - This is a prototype version that uses the ds90ub914a deserialzer and a
    different muxing scheme from more modern variants on the analog IO
    - It is pretty widely used in the Harnett and Wilson labs
2020-10-20 Fix several issues while testing fmc-host rev 1.4
    - VADJ on the FMC connector determines the IO voltage of all the "A"
    pins on the FMC connector, and therefore chips driving or receiving from
    these lines must use VADJ for their IO voltage.
    - The IO voltage of all "B" pins on the FMC connector is determined by
    VIO_B_M2C, so I'm feeding VADJ right back into that pin.
    - The 1.8V core voltage for the deserializers is now derived from VADJ
2021-06-25 Moved fmc-host into independent repo
    - Did some reorganization as well to make it a bit more like the
    onix-headstage-neuropix1 repo
2021-06-26 Update README.md
    - Delete redundant BOM and stackup info that can now be found in fmc-host/README.md
2021-06-26 Replaced revisions folders with tags
    - Tags are rev-1.3 and rev-1.4
2021-06-28 ONIX FMC Host revision 1.5
    - Lots of minor fixes after extensive testing of 1.4
    - VITA-57 compliance
    - Remove debug points
    - Standalone 1.8V regulator for deserializers
    - Lots of other small fixes
2021-07-10 Revision 1.6
    - The major change here is that I've swapped the vertical MVLVDS sync
    header for a through-hole right-angle version that is much more
    amenable to daisy chain connections when the card is in a PCIe slot.
    - Deleted some obsolete, hard to maintain files
    - Deleted some obsolete datasheets
2021-07-17 Move datasheets into fmc-host directory
2021-07-18 Add .gitignore
2021-09-01 Add license
    - CC BY-NC-SA 4.0
2021-10-25 Redesign of the PCIe bracket
    - Fixed incorrect distances
    - Added inserts for 5mm RGB LEDs for better panel lighting to work wirht
    revision 1.6 (Rev. F)
    - Two versions 2.0 mm and 1.27 mm thick. 2.0 is probably the only
    reasonable one for 3D printing.
    - Shapeways DGPA12GB (Dark Grey PA12 with glass beads) has excellent
2021-10-27 Update PCIe bracket after testing
    - Move the FMC supports to the inside and make them solid
    - Make the the portions of the bracket that must interface with the card
    slot thinner to give them a better chance of working (the part should
    really be 0.8mm thick)
2022-03-09 Revision F ready for fabrication feedback
    - Replaced QFN AD5142 with TSSOP package, which is available
    - Added ground pours to all layers
    - Used thermals on top and bottom to improve solderability
2022-04-12 Added 3D printable shell for creating ganged MMCX connection
    - Should make it easier for people to get the coax cable ordering
    correct at host
2022-08-22 Remove 2mm thick PCIe bracket
    - Too thick
    - 1.27 mm version is in spec, and should be used
2023-01-28 Create fmc-host - panel.brd
    Panel is a 2x2 with V-Cut and milling as separation method.
    The distance between individual boards is 5 mm.
2023-01-28 Added gerber files.
2023-03-29 first commit of metal PCIe bracket and LED PCB
    still need to source LEDs for LED PCB - common cathode/independent bottom-entry/revese-mounted LEDS turn out to be rare. PCIe bracket glue is pretty much good to go - LED hole positions are subject t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
2023-03-29 passes osh cut design check
    made a cut at the side 90 deg bend so the bend is like only half as long now. This is so that we don't get insufficient flange support warning
2023-03-30 LED PCB perpendicular to bracket
2023-03-30 added clearance for lens
2023-03-30 engraving finished. part w/ questionable flange to be tested in Oschut
2023-03-30 added logo for engraving if we want
2023-03-30 cleaned up pcie-metal-bracket folder
2023-03-31 production files added (i.e. gerber and dxf)
2023-04-03 gerbers and kicad ready for review
    gerber, bom, pnp files are in production folder for pcb fabrication and assembly. not sure if v-cut will be recognized by jlc. also, the individual pcbs are larger now with LEDs centered
2023-04-04 Update LED panel design after review
    - Reduce size to fit in current allowed volume
    - Move connector for improved strain relief
    - Match RGB pinout on fmc host
2023-04-28 fixed hole spacing, cleaned engraving
2023-04-28 hole diameters
2023-05-05 Fixed PCIe Bracket
    - hole spacing fixed
    - exploratory engravings removed
    - logo moved
    - mmcx hole diameter reduced to avoid thin features
2023-05-05 Fixed Schematic
    - LEDs remapped
    - Mounting pins grounded for mechanical integrity
    - Changed LED symbol (symbol is the same as KiCad generic symbol but
    with renumbered pins)
    - fiber optic included in schematic
2023-07-13 fixed pcb led-connector mapping
    be warned that schematic does not match pcb in an effort to get this to filipe for order asap
2026-03-31 Start KiCAD migration and address rev. F issues
    - Fix clashing reference selection on AD7616
    - Move from AD7617 to AD7616
    - Add TVS diodes to LVDS lines to the breakout board.
2026-05-08 Added OEPS PN
2026-05-28 Updated to latest OEPS PN and upgraded to KiCad 10
2026-06-30 Fix AD761x nRESET input
    - Replace 0.1uF filter capacitor with 100pF
    - Replace series 10k resistor with 0 ohm jumper
    - Add 10k pulldown so that chip power-on defaults to the reset state
